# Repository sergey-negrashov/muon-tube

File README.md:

# MuonTube. Geiger based muon detector for art and science. 
In this project I aim to design and develop a standalone muon detector using old Soviet STS-5  Geiger tubes.  Geometry is shown bellow:

# Roadmap:
1. Power supply design. (Done)
2. Data acquisition design. (Work in progress)
3. Mechanical design. (Started)
4. Integration.

I intend to use custom electronics for the PSU and DAQ. Most likely driven by an FPGA. 
PDF for the PSU and the bias circuit for the GM tube now available [obsolete new one comming soon](https://github.com/sergey-negrashov/muon-tube/raw/master/Schematics/PSU.pdf)

# Goodies 
Geiger tube cage:

Freshly milled HV PSU board:

First Muons?

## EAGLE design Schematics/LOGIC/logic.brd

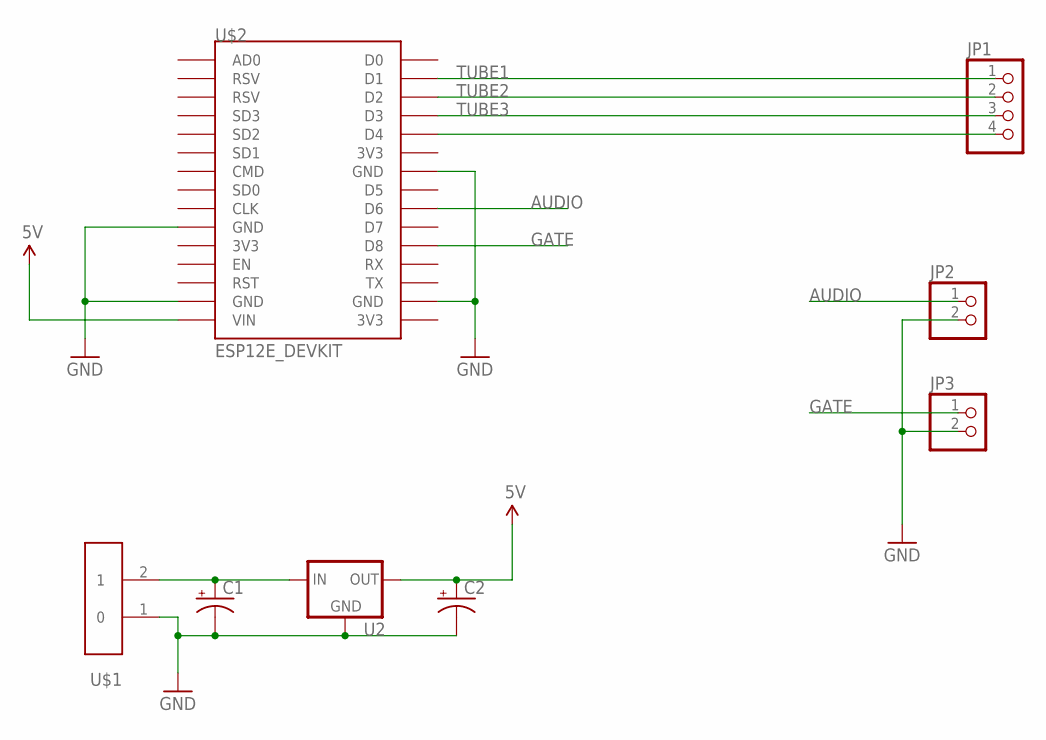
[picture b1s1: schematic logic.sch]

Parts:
C1, C2: 10UF-25V-20%(PTH); CPOL-RADIAL-10UF-25V
JP1: PINHD-1X4; 1X04
JP2, JP3: PINHD-1X2; 1X02
U2: V_REG_78XXSINK; TO220-IGO
U$1: ED2609
U$2: ESP12E_DEVKIT

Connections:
5V: C2.1 (+), U2.OUT, U$2.VIN
AUDIO: JP2.1, U$2.D6
GATE: JP3.1, U$2.D8
GND: C1.2 (-), C2.2 (-), JP2.2, JP3.2, U2.GND, U$1.1 (0), U$2.GND@0 (GND), U$2.GND@1 (GND), U$2.GND@2 (GND), U$2.GND@3 (GND)
unnamed: C1.1 (+), U2.IN, U$1.2 (1)
unnamed: JP1.4, U$2.D4
TUBE1: JP1.1, U$2.D1
TUBE2: JP1.2, U$2.D2
TUBE3: JP1.3, U$2.D3

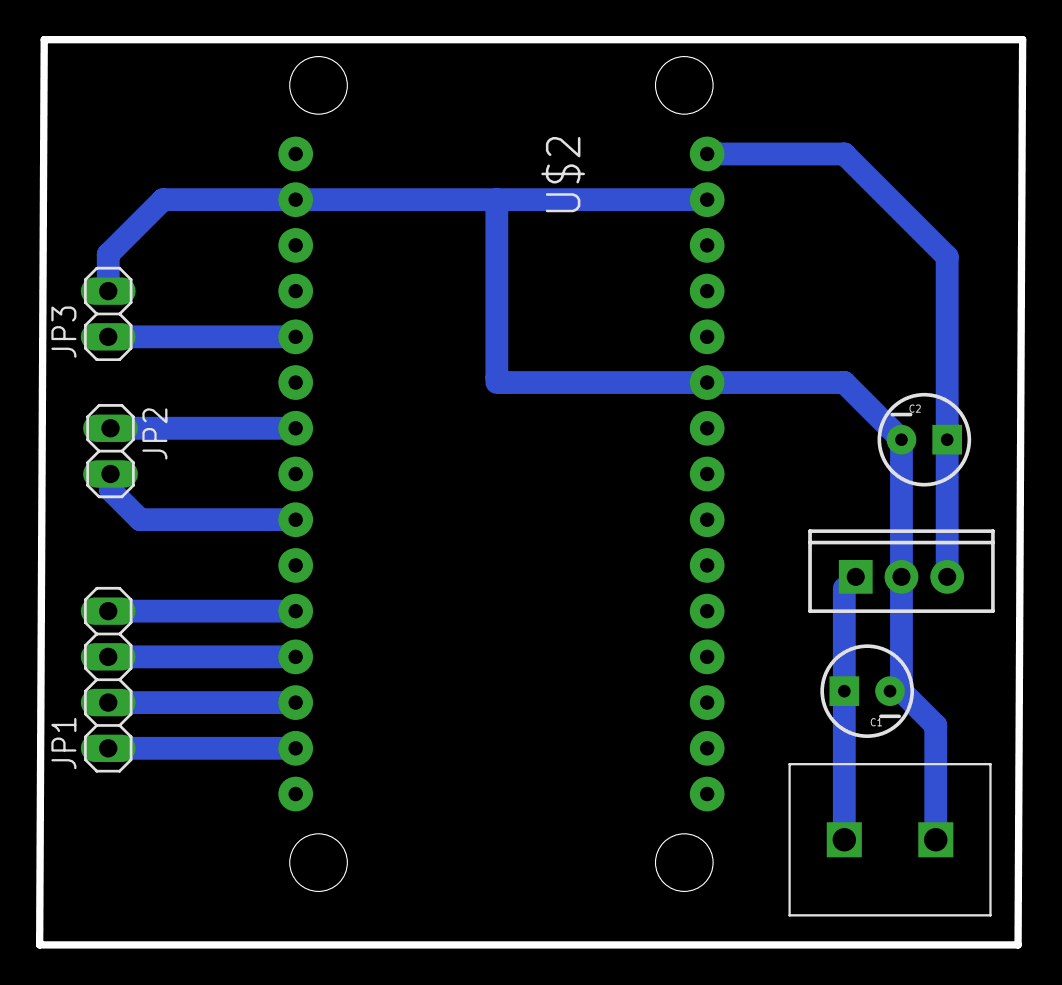
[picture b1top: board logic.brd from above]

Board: 2 copper layers, 54.6 x 50.3 mm, 8 parts (0 on the bottom side), 9 nets.

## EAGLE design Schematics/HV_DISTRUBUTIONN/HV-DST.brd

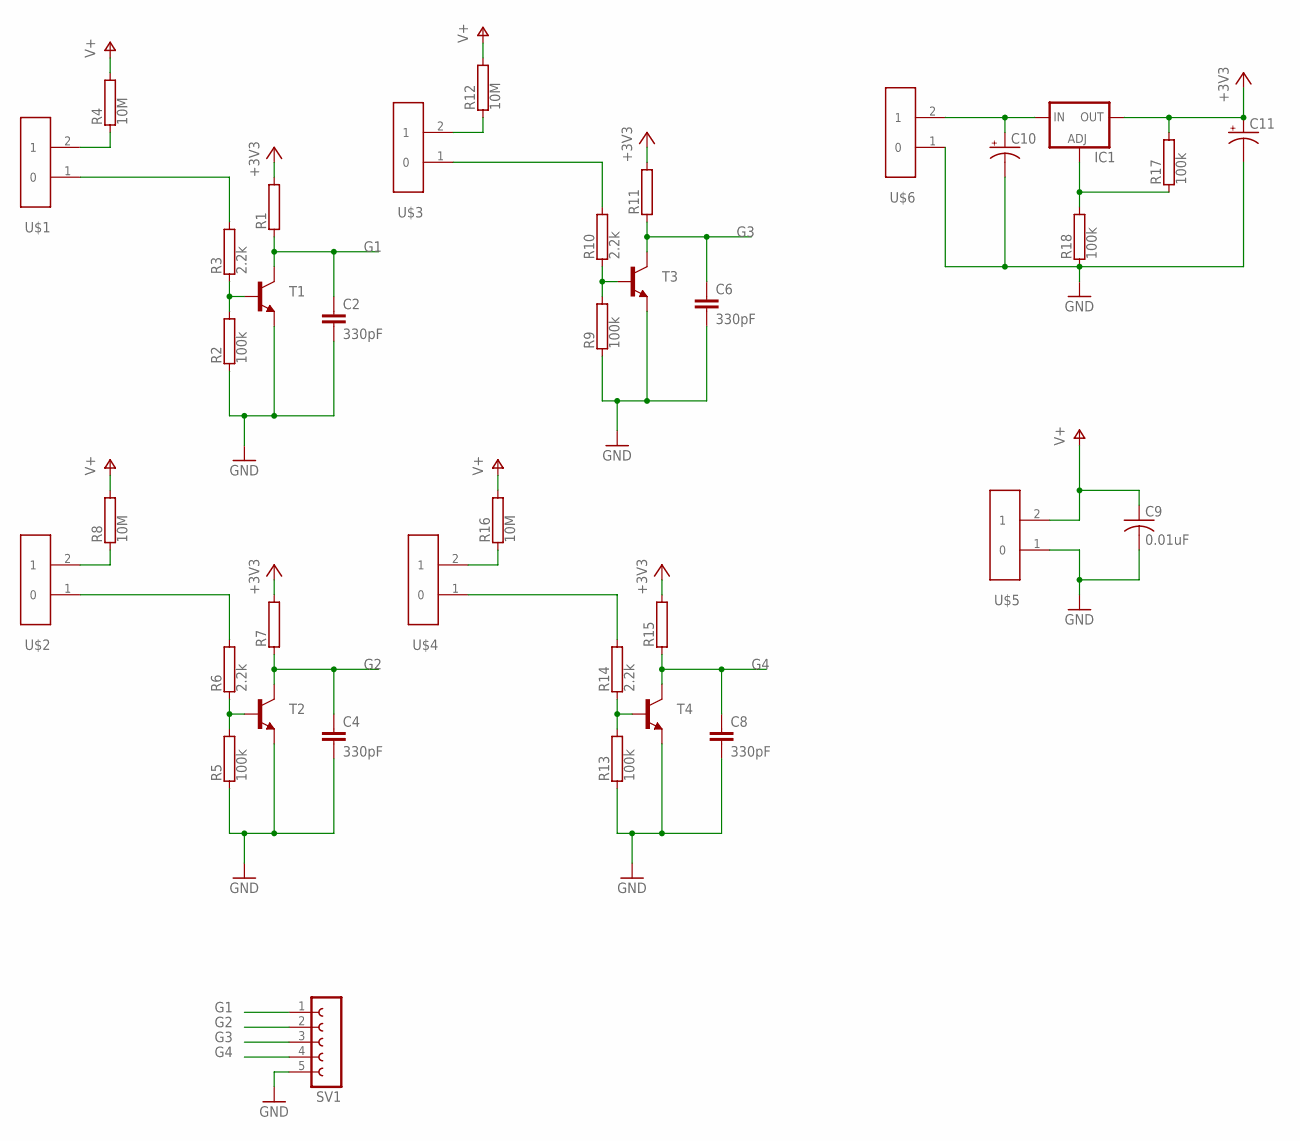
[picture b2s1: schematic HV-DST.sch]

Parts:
C2, C4, C6, C8: 330pF; C2.5-2
C9: 0.01uF; C075-032X103
C10, C11: CPOL-USE2.5-5; E2,5-5
IC1: LM317TS; 317TS
R1, R7, R11, R15: RRS1/4; RS1/4
R2, R5, R9, R13, R17, R18: 100k; RS1/4
R3, R6, R10, R14: 2.2k; RS1/4
R4, R8, R12, R16: 10M; RS1/4
SV1: FE05-1
T1, T2, T3, T4: 2N5551-NPN-TO92-CBE; TO92-CBE
U$1, U$2, U$3, U$4, U$5, U$6: ED2609

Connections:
+3V3: C11.+, IC1.2 (OUT), R1.2, R7.2, R11.2, R15.2, R17.2
G1: C2.1, R1.1, SV1.1, T1.C
G2: C4.1, R7.1, SV1.2, T2.C
G3: C6.1, R11.1, SV1.3, T3.C
G4: C8.1, R15.1, SV1.4, T4.C
GND: C2.2, C4.2, C6.2, C8.2, C9.2, C10.-, C11.-, R2.1, R5.1, R9.1, R13.1, R18.1, SV1.5, T1.E, T2.E, T3.E, T4.E, U$5.1 (0), U$6.1 (0)
unnamed: R2.2, R3.1, T1.B
unnamed: R3.2, U$1.1 (0)
unnamed: C10.+, IC1.3 (IN), U$6.2 (1)
unnamed: R4.1, U$1.2 (1)
unnamed: R5.2, R6.1, T2.B
unnamed: R6.2, U$2.1 (0)
unnamed: R8.1, U$2.2 (1)
unnamed: R9.2, R10.1, T3.B
unnamed: R10.2, U$3.1 (0)
unnamed: IC1.1 (ADJ), R17.1, R18.2
unnamed: R12.1, U$3.2 (1)
unnamed: R13.2, R14.1, T4.B
unnamed: R14.2, U$4.1 (0)
unnamed: R16.1, U$4.2 (1)
V+: C9.1, R4.2, R8.2, R12.2, R16.2, U$5.2 (1)

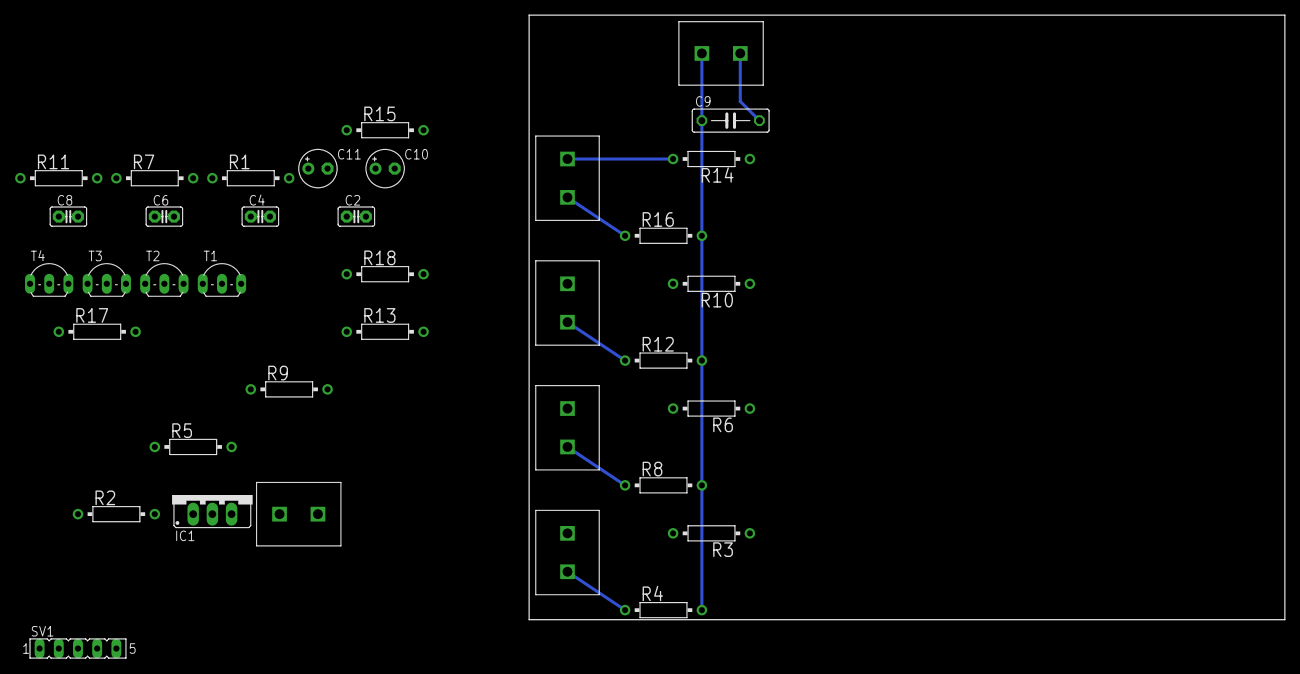
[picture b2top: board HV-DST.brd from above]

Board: 2 copper layers, 100.0 x 80.0 mm, 37 parts (0 on the bottom side), 21 nets.

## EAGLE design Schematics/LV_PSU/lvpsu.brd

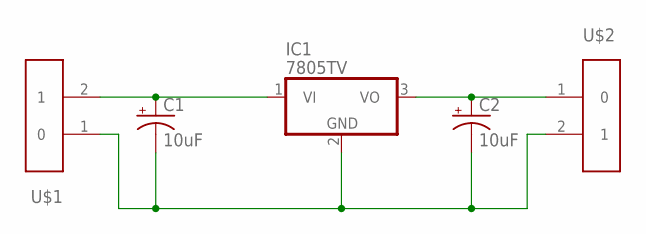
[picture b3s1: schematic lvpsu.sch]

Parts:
C1, C2: 10uF; E2,5-5
IC1: 7805TV; TO220V
U$1, U$2: ED2609

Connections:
unnamed: C1.+, IC1.1 (VI), U$1.2 (1)
unnamed: C2.+, IC1.3 (VO), U$2.1 (0)
unnamed: C1.-, C2.-, IC1.2 (GND), U$1.1 (0), U$2.2 (1)

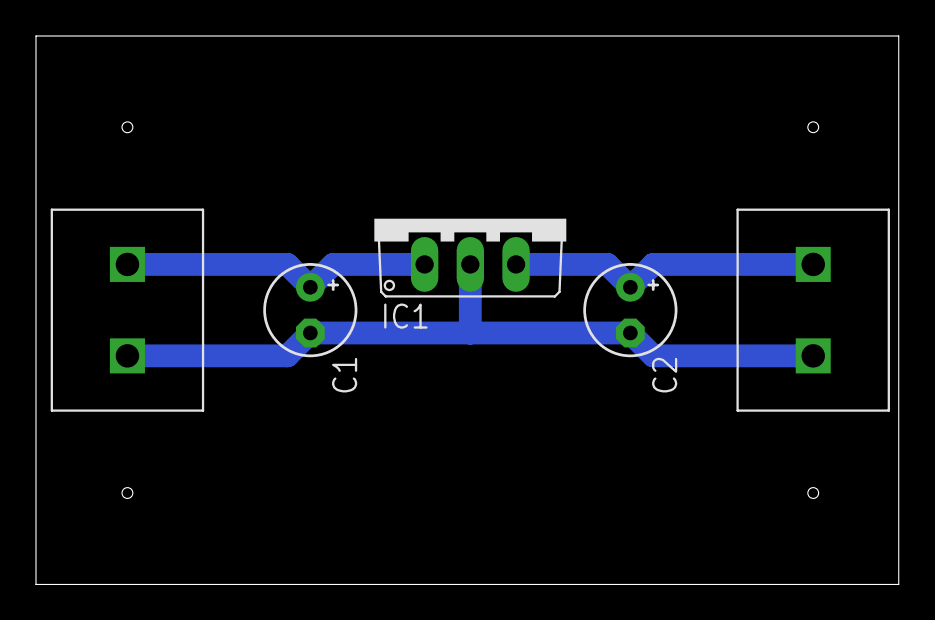
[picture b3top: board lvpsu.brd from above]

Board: 2 copper layers, 47.9 x 30.5 mm, 5 parts (0 on the bottom side), 3 nets.

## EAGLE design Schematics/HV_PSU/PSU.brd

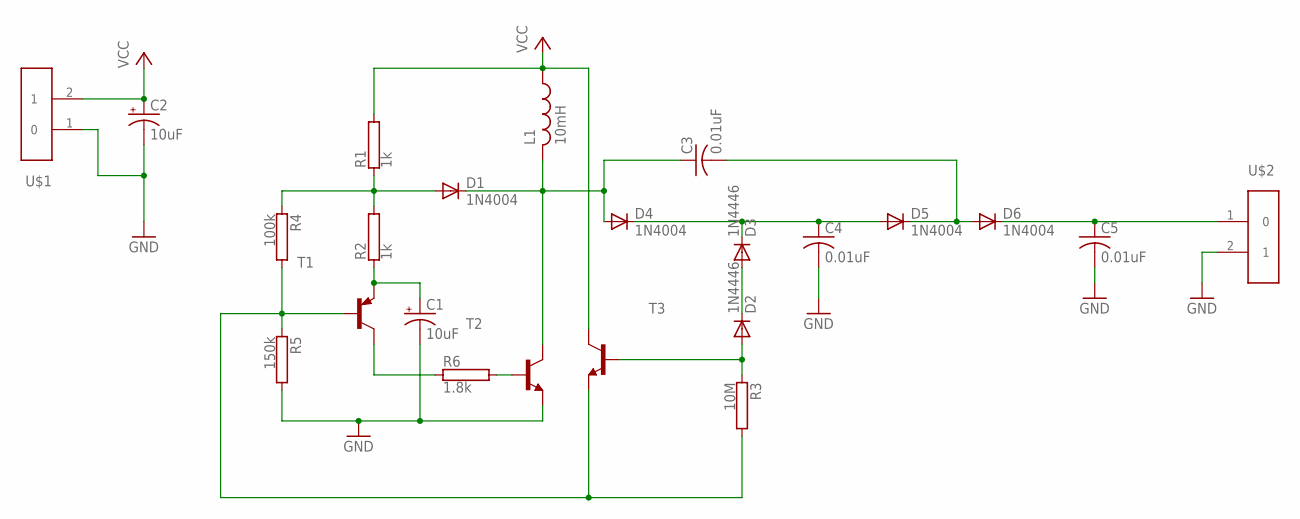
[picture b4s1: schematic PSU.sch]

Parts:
C1, C2: 10uF; E2,5-5
C3, C4, C5: 0.01uF; C075-032X103
D1, D4, D5, D6: 1N4004; DO41-10
D2, D3: 1N4446; DO35-10
L1: 10mH; 0207/5V
R1, R2: 1k; RS1/4
R3: 10M; RS1/4
R4: 100k; RS1/4
R5: 150k; RS1/4
R6: 1.8k; RS1/4
T1: 2N4403-PNP-TO92-EBC; TO92-EBC
T2: MPSA42-NPN-TO92-EBC; TO92-EBC
T3: MPSA18-NPN-TO92-EBC; TO92-EBC
U$1, U$2: ED2609

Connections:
GND: C1.-, C2.-, C4.2, C5.2, R5.2, T2.E, U$1.1 (0), U$2.2 (1)
unnamed: D1.A, R1.1, R2.2, R4.1
unnamed: D2.A, R3.1, T3.B
unnamed: R3.2, R4.2, R5.1, T1.B, T3.E
unnamed: C1.+, R2.1, T1.E
unnamed: D2.C, D3.A
unnamed: R6.2, T2.B
unnamed: C3.1, D1.C, D4.A, L1.2, T2.C
unnamed: R6.1, T1.C
unnamed: C4.1, D3.C, D4.C, D5.A
unnamed: C3.2, D5.C, D6.A
unnamed: C5.1, D6.C, U$2.1 (0)
VCC: C2.+, L1.1, R1.2, T3.C, U$1.2 (1)

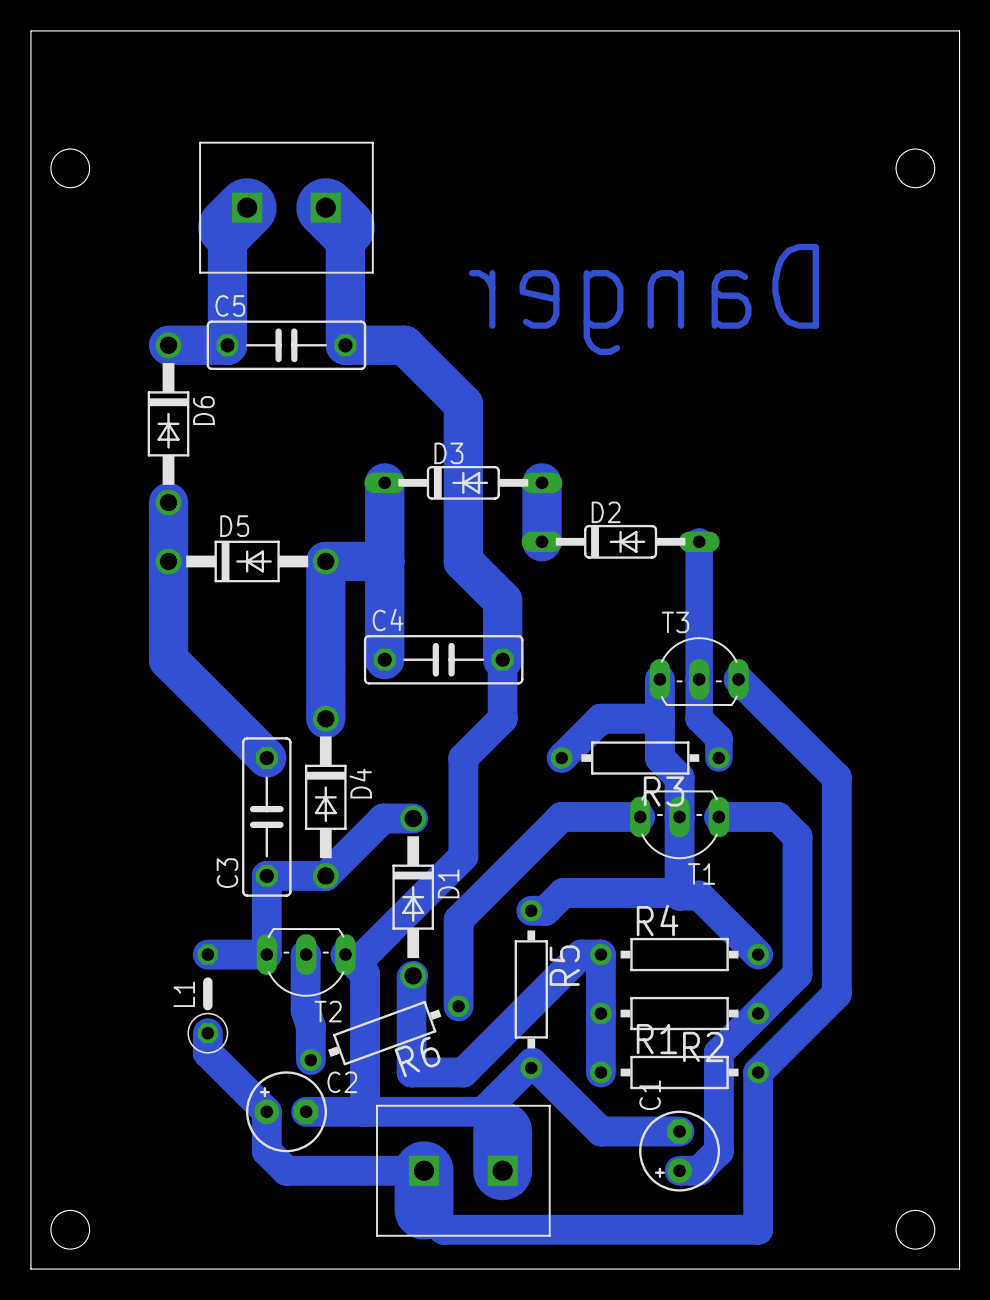
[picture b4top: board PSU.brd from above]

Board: 2 copper layers, 60.0 x 80.0 mm, 23 parts (0 on the bottom side), 13 nets.

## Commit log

2016-01-20 Initial import for the schematics
    Setting up the project directory.
2016-01-20 First crack at readme
2016-01-23 added the library
2016-02-01 Finalized the design for the Geiger supply/readout
2016-02-02 Fixed the cap values in the voltage multiplier
2016-02-24 Added layout
2016-03-17 Gieger tubes are in
2016-03-31 Added the milled PSU board drawing
2016-04-23 HV PSU eagle
2016-04-23 out with the old
2016-04-23 Cleaning up
2016-04-23 CNC files
2016-04-30 Working on the HV distribution board and discriminator
2016-05-03 Added a 5V degulator PCB.
2016-05-10 First Muon
2016-05-14 Working on layout for distribution
2016-05-14 Finished routing
2016-05-14 Fixed Typo
2016-06-10 Logic board based on ESP12e
2016-07-07 Had to redo this board. Could not do 8mill traces on my mill

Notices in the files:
parts and their libraries:
SparkFun-PowerIC: Licensing: Creative Commons ShareAlike 4.0 International - https://creativecommons.org/licenses/by-sa/4.0
